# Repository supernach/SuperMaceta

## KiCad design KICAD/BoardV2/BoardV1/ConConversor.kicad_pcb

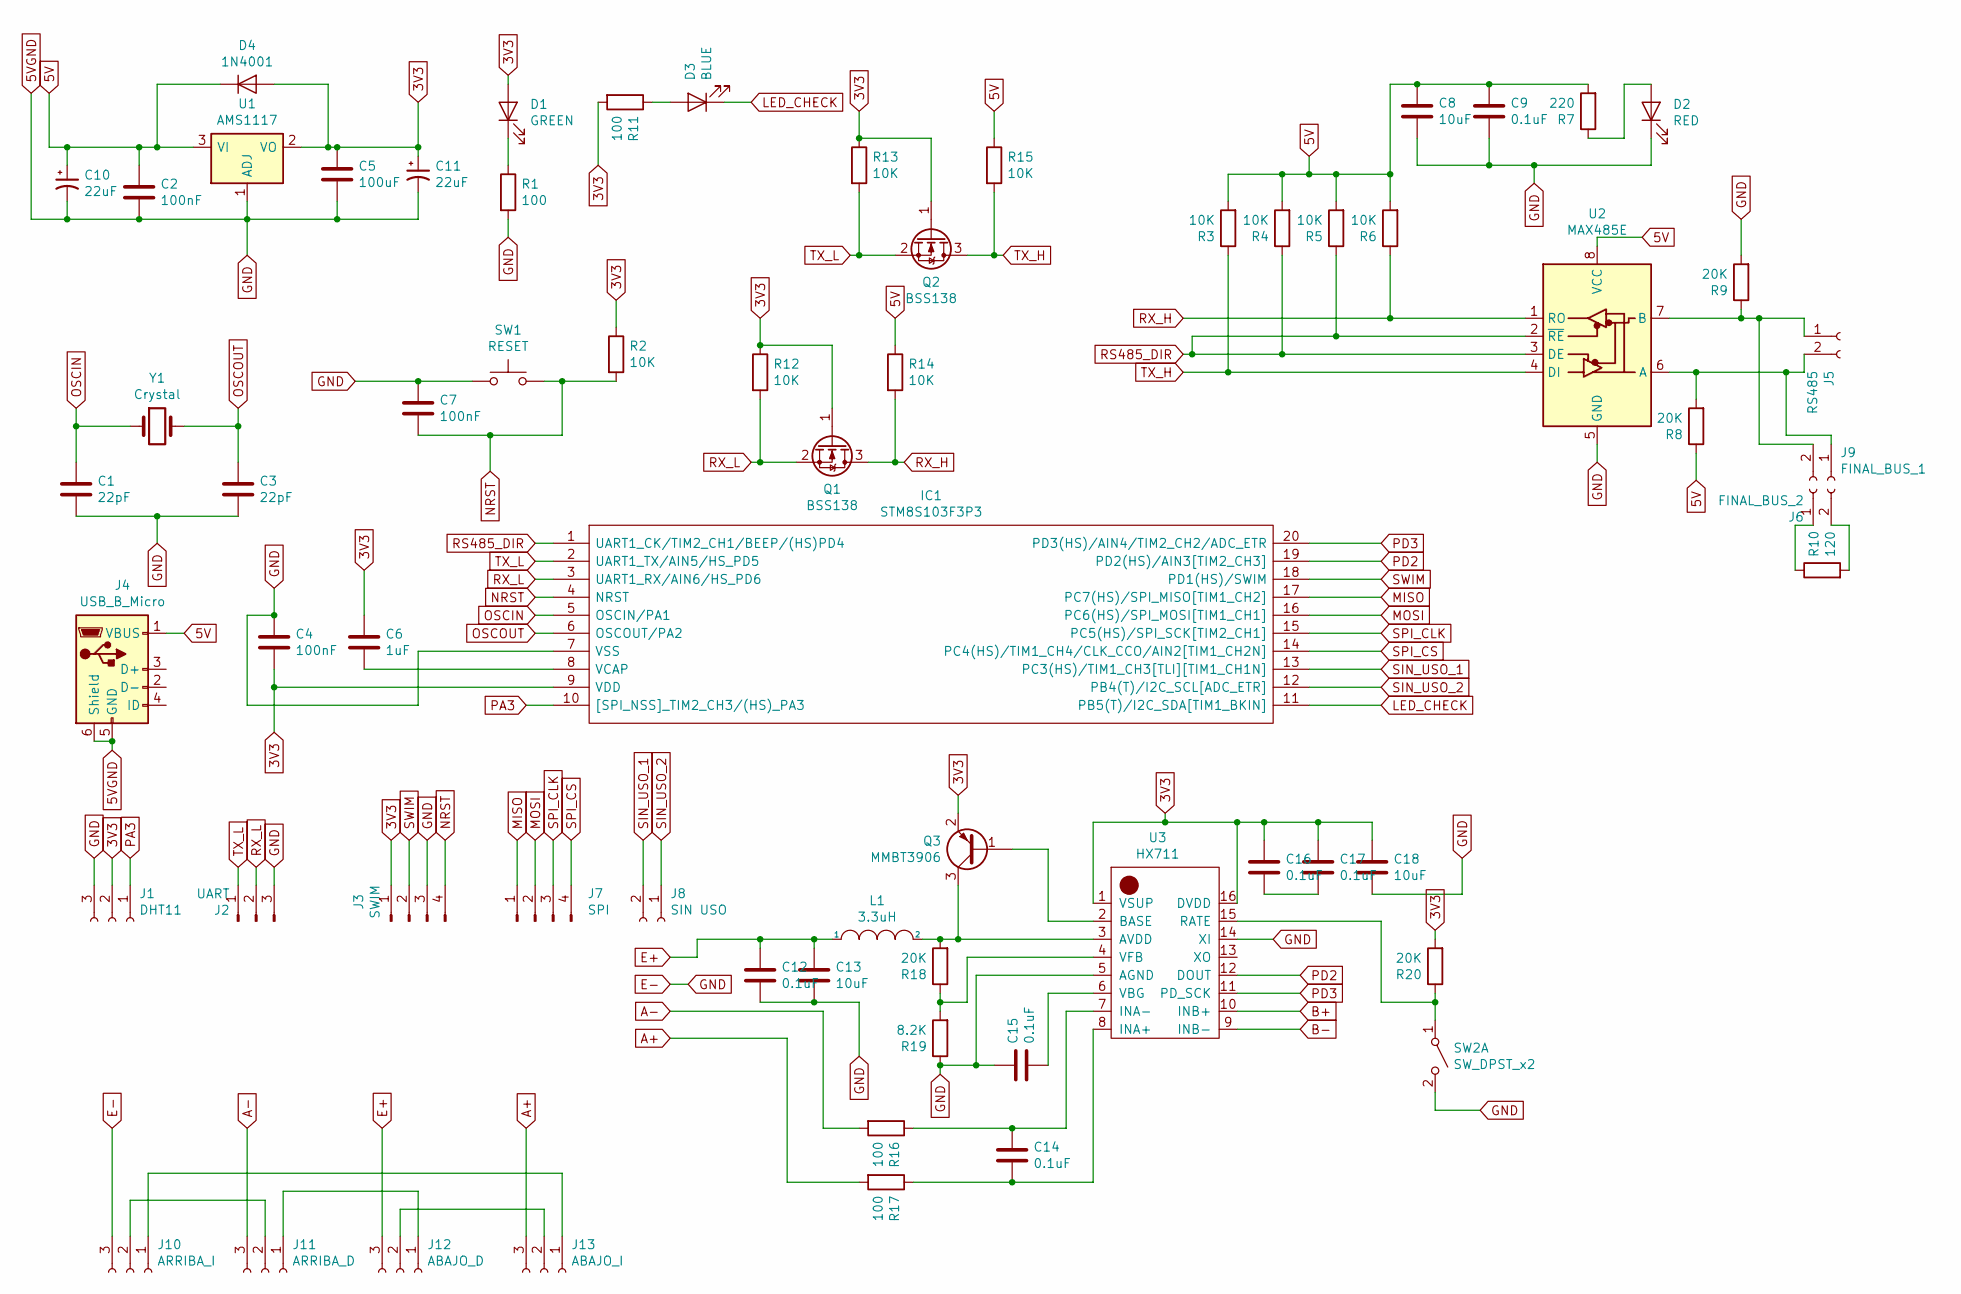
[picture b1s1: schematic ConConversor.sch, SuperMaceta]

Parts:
C1, C3: 22pF; C_0805_2012Metric
C2, C4, C7: 100nF; C_0805_2012Metric
C5: 100uF; C_0805_2012Metric
C6: 1uF; C_0805_2012Metric
C8, C13, C18: 10uF; C_0805_2012Metric
C9, C12, C14, C15, C16, C17: 0.1uF; C_0805_2012Metric
C10, C11: 22uF; CP_Elec_4x5.4
D1: GREEN; LED_0805_2012Metric
D2: RED; LED_0805_2012Metric
D3: BLUE; LED_0805_2012Metric
D4: 1N4001; D_DO-41_SOD81_P10.16mm_Horizontal
IC1: STM8S103F3P3; SOP65P640X120-20N; Manufacturer_Part_Number STM8S103F3P3; Mouser Part Number 511-STM8S103F3P3
J1: DHT11; JST_EH_S3B-EH_1x03_P2.50mm_Horizontal
J2: UART; JST_PH_B3B-PH-K_1x03_P2.00mm_Vertical
J3: SWIM; PinHeader_1x04_P2.54mm_Vertical
J4: USB_B_Micro; USB_Micro-AB_Molex_47590-0001
J5: RS485; JST_EH_S2B-EH_1x02_P2.50mm_Horizontal
J6: FINAL_BUS_2; PinHeader_1x02_P2.54mm_Vertical
J7: SPI; JST_PH_B4B-PH-K_1x04_P2.00mm_Vertical
J8: SIN USO; PinHeader_1x02_P2.54mm_Vertical
J9: FINAL_BUS_1; PinHeader_1x02_P2.54mm_Vertical
J10: ARRIBA_I; JST_EH_S3B-EH_1x03_P2.50mm_Horizontal
J11: ARRIBA_D; JST_EH_S3B-EH_1x03_P2.50mm_Horizontal
J12: ABAJO_D; JST_EH_S3B-EH_1x03_P2.50mm_Horizontal
J13: ABAJO_I; JST_EH_S3B-EH_1x03_P2.50mm_Horizontal
L1: 3.3uH; L_0805_2012Metric
Q1, Q2: BSS138; SOT-23
Q3: MMBT3906; SOT-23
R1, R11, R16, R17: 100; R_0805_2012Metric
R2, R3, R4, R5, R6, R12, R13, R14, R15: 10K; R_0805_2012Metric
R7: 220; R_0805_2012Metric
R8, R9, R18, R20: 20K; R_0805_2012Metric
R10: 120; R_0805_2012Metric
R19: 8.2K; R_0805_2012Metric
SW1: RESET; SW_SPST_CK_RS282G05A3
SW2: SW_DPST_x2; SW_DIP_SPSTx01_Slide_6.7x4.1mm_W6.73mm_P2.54mm_LowProfile_J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
U1: AMS1117; SOT-223-3_TabPin2
U2: MAX485E; SOIC-8-1EP_3.9x4.9mm_P1.27mm_EP2.29x3mm
U3: HX711; HX711_SOP16L
Y1: Crystal; Crystal_HC49-4H_Vertical

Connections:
3V3: C4.1, C5.1, C6.1, C11.1, C16.1, C17.1, C18.1, D1.2 (A), D4.2 (A), IC1.9 (VDD), J1.2, J3.1, Q1.1 (G), Q2.1 (G), Q3.2 (E), R2.1, R11.2, R12.1, R13.1, R20.2, U1.2 (VO), U3.1 (VSUP), U3.16 (DVDD)
5V: C2.1, C8.1, C9.1, C10.1, D4.1 (K), J4.1 (VBUS), R3.2, R4.2, R5.2, R6.2, R7.2, R8.1, R14.1, R15.1, U1.3 (VI), U2.8 (VCC)
5VGND: C1.2, C2.2, C3.2, C4.2, C5.2, C7.1, C8.2, C9.2, C10.2, C11.2, C12.2, C13.2, C15.1, C18.2, D2.1 (K), IC1.7 (VSS), J1.3, J2.3, J3.3, J4.5 (GND), J4.6 (Shield), J10.3, R1.2, R9.2, R19.1, SW1.1, SW2.2 (B), U1.1 (ADJ), U2.5 (GND), U3.5 (AGND), U3.14 (XI)
A+: J13.3, R17.2
A-: J11.3, R16.2
B+: U3.10 (INB+)
B-: U3.9 (INB-)
E+: C12.1, C13.1, J12.3, L1.1
LED_CHECK: D3.1 (K), IC1.11 (PB5(T)/I2C_SDA[TIM1_BKIN])
MISO: IC1.17 (PC7(HS)/SPI_MISO[TIM1_CH2]), J7.1
MOSI: IC1.16 (PC6(HS)/SPI_MOSI[TIM1_CH1]), J7.2
NRST: C7.2, IC1.4 (NRST), J3.4, R2.2, SW1.2
unnamed: C6.2, IC1.8 (VCAP)
unnamed: C14.1, R16.1, U3.7 (INA-)
unnamed: C14.2, R17.1, U3.8 (INA+)
unnamed: C15.2, U3.6 (VBG)
unnamed: C16.2, C17.2
unnamed: D1.1 (K), R1.1
unnamed: D2.2 (A), R7.1
unnamed: D3.2 (A), R11.1
unnamed: J5.1, J9.2, R9.1, U2.7 (B)
unnamed: J5.2, J9.1, R8.2, U2.6 (A)
unnamed: J6.1, R10.1
unnamed: J6.2, R10.2
unnamed: J10.1, J13.1
unnamed: J10.2, J11.2
unnamed: J11.1, J12.1
unnamed: J12.2, J13.2
unnamed: L1.2, Q3.3 (C), R18.2, U3.3 (AVDD)
unnamed: Q3.1 (B), U3.2 (BASE)
unnamed: R18.1, R19.2, U3.4 (VFB)
unnamed: R20.1, SW2.1 (A), U3.15 (RATE)
OSCIN: C1.1, IC1.5 (OSCIN/PA1), Y1.1
OSCOUT: C3.1, IC1.6 (OSCOUT/PA2), Y1.2
PA3: IC1.10 ([SPI_NSS]_TIM2_CH3/(HS)_PA3), J1.1
PD2: IC1.19 (PD2(HS)/AIN3[TIM2_CH3]), U3.12 (DOUT)
PD3: IC1.20 (PD3(HS)/AIN4/TIM2_CH2/ADC_ETR), U3.11 (PD_SCK)
RS485_DIR: IC1.1 (UART1_CK/TIM2_CH1/BEEP/(HS)PD4), R4.1, R5.1, U2.2 (~RE), U2.3 (DE)
RX_H: Q1.3 (D), R6.1, R14.2, U2.1 (RO)
RX_L: IC1.3 (UART1_RX/AIN6/HS_PD6), J2.2, Q1.2 (S), R12.2
SIN_USO_1: IC1.13 (PC3(HS)/TIM1_CH3[TLI][TIM1_CH1N]), J8.2
SIN_USO_2: IC1.12 (PB4(T)/I2C_SCL[ADC_ETR]), J8.1
SPI_CLK: IC1.15 (PC5(HS)/SPI_SCK[TIM2_CH1]), J7.3
SPI_CS: IC1.14 (PC4(HS)/TIM1_CH4/CLK_CCO/AIN2[TIM1_CH2N]), J7.4
SWIM: IC1.18 (PD1(HS)/SWIM), J3.2
TX_H: Q2.3 (D), R3.1, R15.2, U2.4 (DI)
TX_L: IC1.2 (UART1_TX/AIN5/HS_PD5), J2.1, Q2.2 (S), R13.2

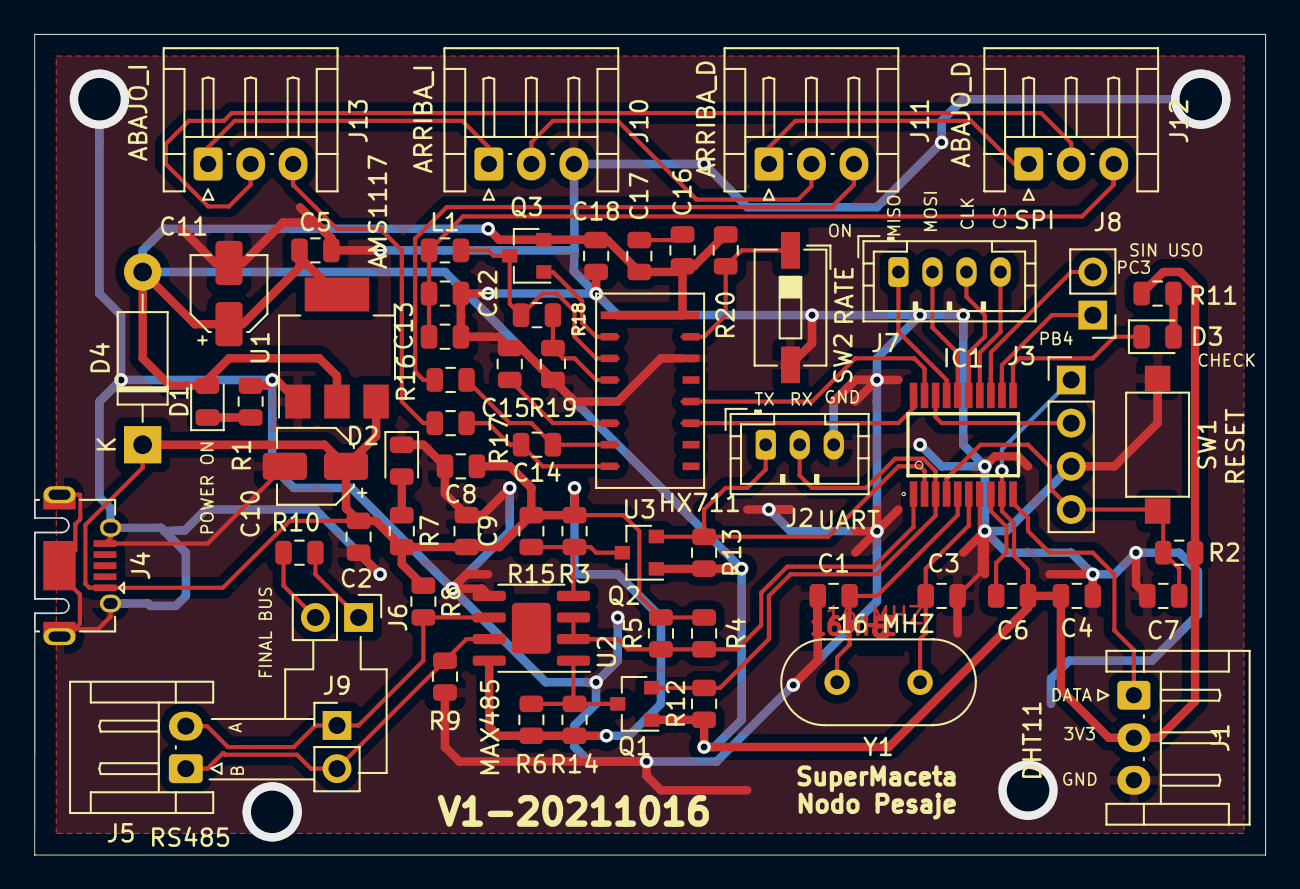
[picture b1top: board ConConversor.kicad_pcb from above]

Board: 2 copper layers, 72.4 x 48.2 mm, 66 parts (0 on the bottom side), 45 nets.

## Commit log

2021-09-09 20210909
2021-09-11 20210911
2021-09-19 20210919
2021-09-20 20210920
2021-09-21 20210921
2021-09-22 20210922
2021-09-23 20210923
2021-10-09 20211009
2021-10-22 20211022
2021-10-31 20211101
